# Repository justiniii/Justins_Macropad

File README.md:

# Justins_Macropad

A 5-key macropad with RGB underglow and OLED display, built around the Seeed XIAO RP2040. Designed for general shortcuts and everyday productivity. Macropad was designed off a sketch of my fingers so its perfectly ergonomic :)

---

## Challenges

This is my first PCB I am planning to manufacture, I used fusion to create the layout using a dxf using a sketch on paper. The keys are positioned to the size and position of my hand. After multiple changes I was eventually happy with the result. Fusion360 was used for 3D modelling with no issues.

---

## Schematic

---

## PCB

---

## Case

3D printed two-part case designed to fit the PCB securely, with M3 mounting holes for assembly.

---

## Bill of Materials (BOM)

| Component | Designator | Footprint | Quantity |
|-----------|------------|-----------|----------|
| Seeed XIAO RP2040 | U1 | XIAO-Generic-Hybrid-14P-2.54-21X17.8MM | 1 |
| SK6812MINI RGB LED | D1–D6 | MX_SK6812MINI-E | 6 |
| Cherry MX Push Button Switch | SW1–SW5 | SW_Cherry_MX_1.00u_PCB | 5 |
| SSD1306 128x64 OLED Display | Brd1 | 128x64OLED | 1 |
| M3 Mounting Hole (3.2mm Pad) | H1–H4 | MountingHole_3.2mm_Pad | 4 |
| M3 Screws | — | — | 4 |
| M3 Heat Inserts | — | — | 4 |
| 3D Printed Case | — | — | 1 |

---

## Firmware

This macropad runs [KMK](https://github.com/KMKfw/kmk_firmware) on CircuitPython.

### Setup

1. Flash CircuitPython from [circuitpython.org/board/seeeduino_xiao_rp2040](https://circuitpython.org/board/seeeduino_xiao_rp2040)
2. Copy the `kmk` folder to your `CIRCUITPY` drive
3. Copy `main.py` to the root of your `CIRCUITPY` drive

### Pin Mapping

| Switch | XIAO Pin | GPIO |
|--------|----------|------|
| SW1 | D10 | GP4 |
| SW2 | D9 | GP3 |
| SW3 | D8 | GP2 |
| SW4 | D7 | GP1 |
| SW5 | D2 | GP28 |
| RGB Data | D1 | GP27 |
| OLED SDA | D4 | GP6 |
| OLED SCL | D5 | GP7 |

---

## License

Open source hardware. Feel free to use, modify, and build on this project!

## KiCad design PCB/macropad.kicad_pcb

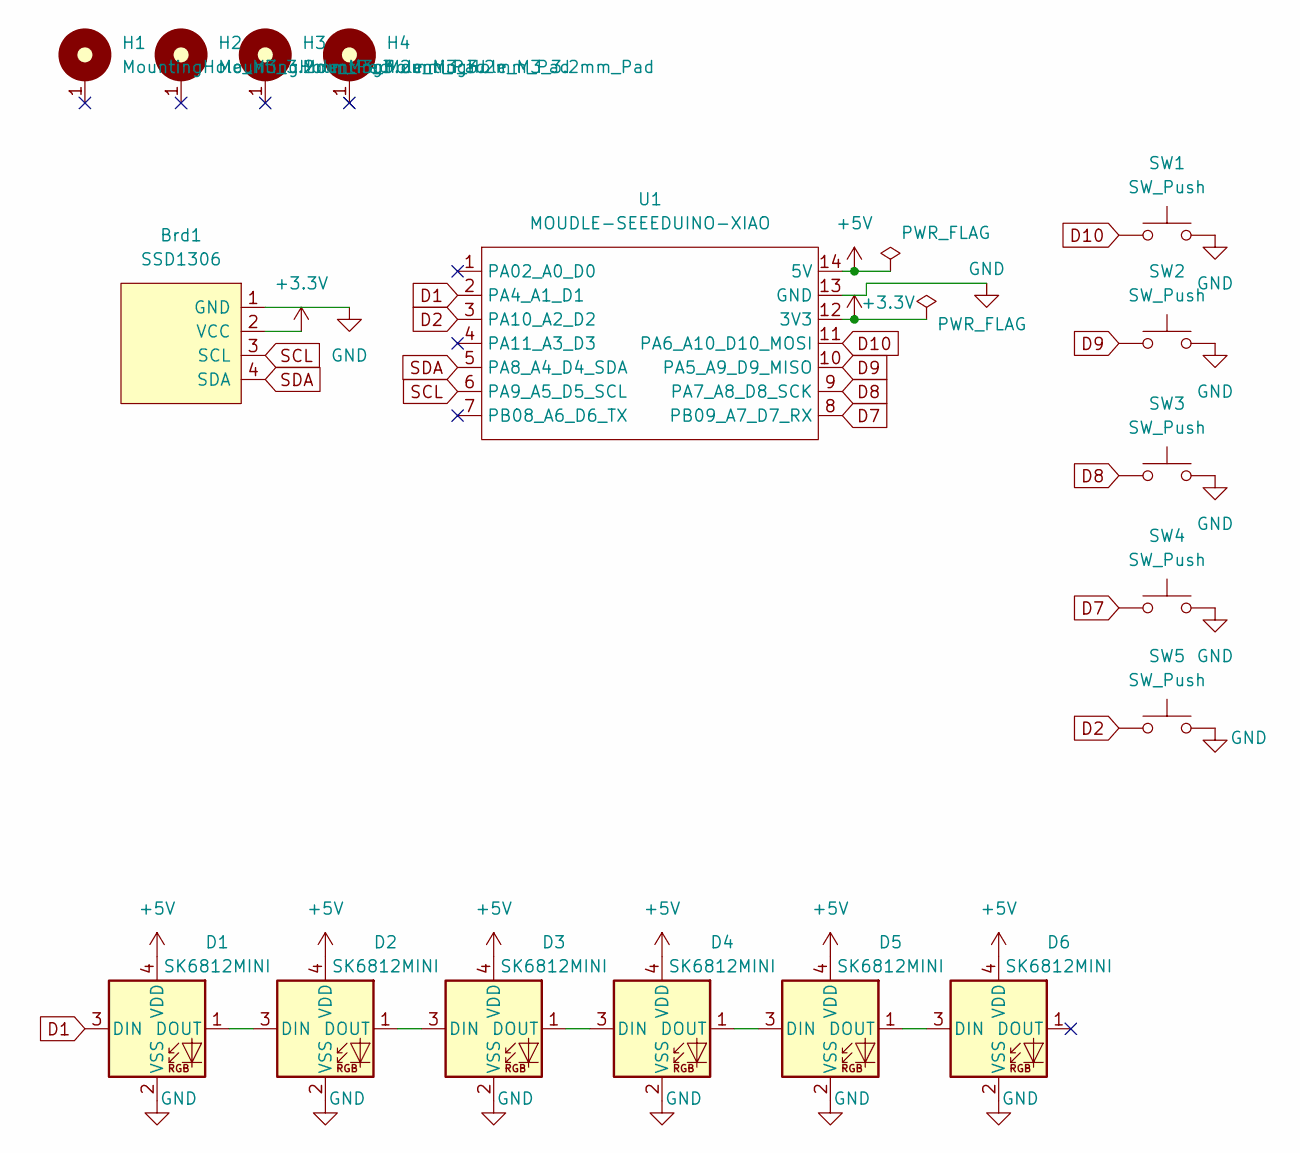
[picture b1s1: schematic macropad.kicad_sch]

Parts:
Brd1: SSD1306; 128x64OLED
D1, D2, D3, D4, D5, D6: SK6812MINI; MX_SK6812MINI-E
H1, H2, H3, H4: MountingHole_M3_3.2mm_Pad; MountingHole_3.2mm_Pad
SW1, SW2, SW3, SW4, SW5: SW_Push; SW_Cherry_MX_1.00u_PCB
U1: MOUDLE-SEEEDUINO-XIAO; XIAO-Generic-Hybrid-14P-2.54-21X17.8MM

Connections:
+3.3V: Brd1.2 (VCC), U1.12 (3V3)
+5V: D1.4 (VDD), D2.4 (VDD), D3.4 (VDD), D4.4 (VDD), D5.4 (VDD), D6.4 (VDD), U1.14 (5V)
D1: D1.3 (DIN), U1.2 (PA4_A1_D1)
D2: SW5.1, U1.3 (PA10_A2_D2)
D7: SW4.1, U1.8 (PB09_A7_D7_RX)
D8: SW3.1, U1.9 (PA7_A8_D8_SCK)
D9: SW2.1, U1.10 (PA5_A9_D9_MISO)
D10: SW1.1, U1.11 (PA6_A10_D10_MOSI)
GND: Brd1.1 (GND), D1.2 (VSS), D2.2 (VSS), D3.2 (VSS), D4.2 (VSS), D5.2 (VSS), D6.2 (VSS), SW1.2, SW2.2, SW3.2, SW4.2, SW5.2, U1.13 (GND)
unnamed: D1.1 (DOUT), D2.3 (DIN)
unnamed: D2.1 (DOUT), D3.3 (DIN)
unnamed: D3.1 (DOUT), D4.3 (DIN)
unnamed: D4.1 (DOUT), D5.3 (DIN)
unnamed: D5.1 (DOUT), D6.3 (DIN)
SCL: Brd1.3 (SCL), U1.6 (PA9_A5_D5_SCL)
SDA: Brd1.4 (SDA), U1.5 (PA8_A4_D4_SDA)

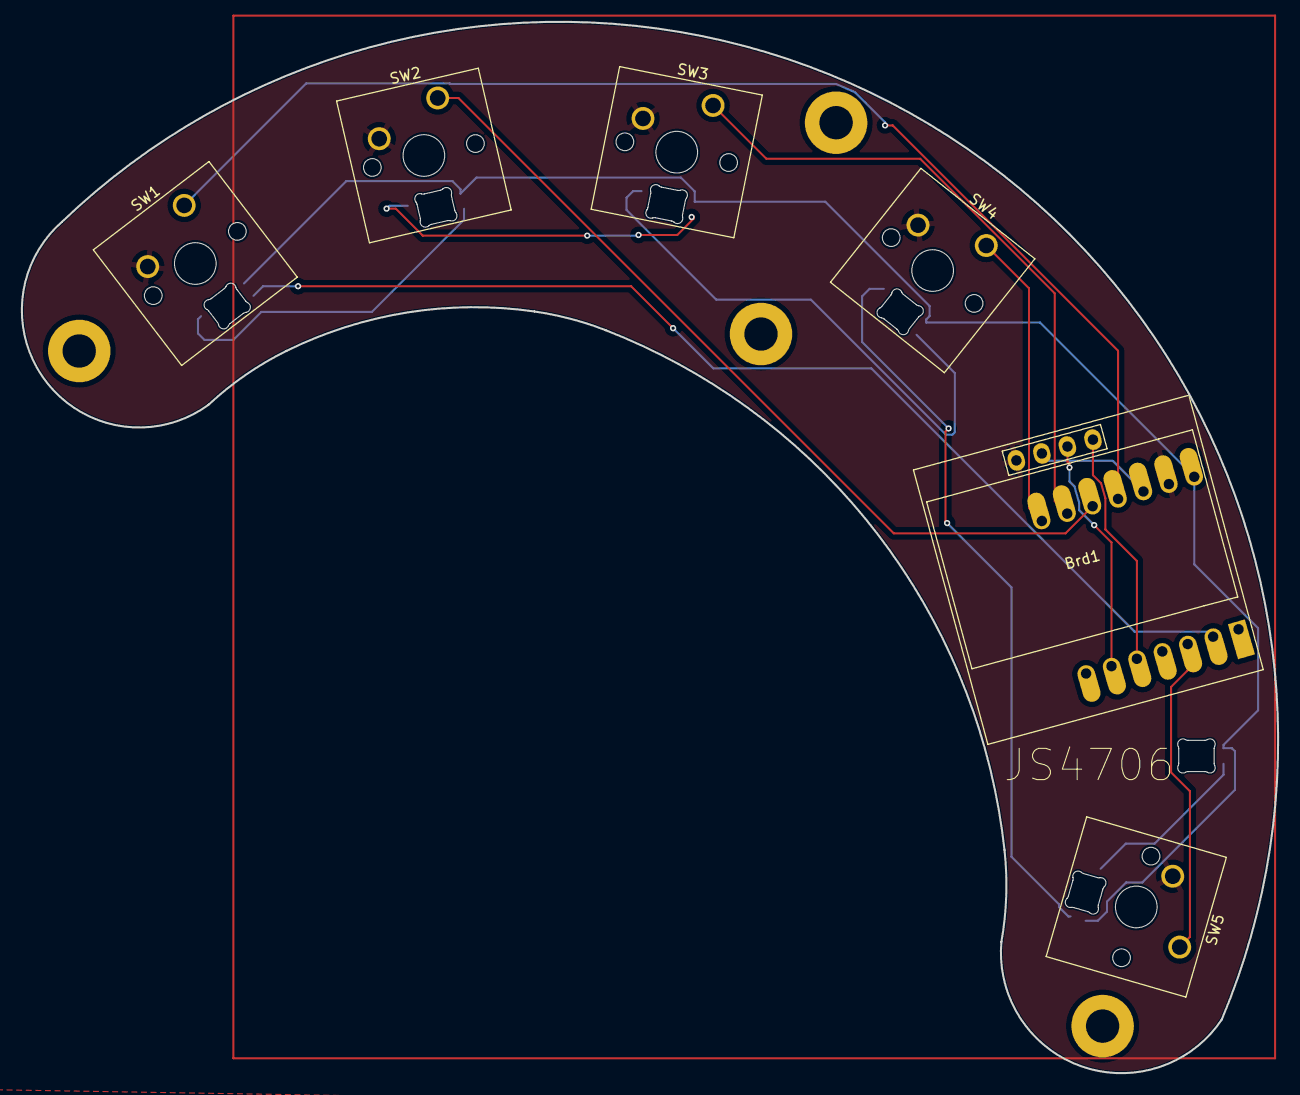
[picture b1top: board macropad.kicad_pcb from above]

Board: 2 copper layers, 120.6 x 100.9 mm, 17 parts (1 on the bottom side), 16 nets.

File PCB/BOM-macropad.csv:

Comment,Designator,Footprint,LCSC,Quantity
SK6812MINI,D6,MX_SK6812MINI-E,,1
SK6812MINI,D5,MX_SK6812MINI-E,,1
SK6812MINI,D4,MX_SK6812MINI-E,,1
SK6812MINI,D3,MX_SK6812MINI-E,,1
SK6812MINI,D2,MX_SK6812MINI-E,,1
SK6812MINI,D1,MX_SK6812MINI-E,,1
MountingHole_M3_3.2mm_Pad,H1,MountingHole_3.2mm_Pad,,1
MountingHole_M3_3.2mm_Pad,H2,MountingHole_3.2mm_Pad,,1
SW_Push,SW3,SW_Cherry_MX_1.00u_PCB,,1
SW_Push,SW5,SW_Cherry_MX_1.00u_PCB,,1
SSD1306,Brd1,128x64OLED,,1
MountingHole_M3_3.2mm_Pad,H4,MountingHole_3.2mm_Pad,,1
SW_Push,SW2,SW_Cherry_MX_1.00u_PCB,,1
SW_Push,SW1,SW_Cherry_MX_1.00u_PCB,,1
SW_Push,SW4,SW_Cherry_MX_1.00u_PCB,,1
MountingHole_M3_3.2mm_Pad,H3,MountingHole_3.2mm_Pad,,1
MOUDLE-SEEEDUINO-XIAO,U1,XIAO-Generic-Hybrid-14P-2.54-21X17.8MM,,1

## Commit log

2026-02-28 initial upload
2026-03-06 All required files uploaded
2026-03-07 added specific files
2026-03-07 fixed missing images
2026-03-08 fixed typo
2026-03-08 moved files
